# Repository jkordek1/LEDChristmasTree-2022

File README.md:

# LEDChristmasTree-2022

## About
LED Christmas tree powered by 2xAAA batteries. It uses self-flashing LEDs (fast and slow). Device draws ~5 mA of current so the batteries should last through holidays!

There are a lot of LED christmas trees but this one is just a perfect size, uses small amount of power and it gives a really nice effect.

## GIFs and images

## YouTube
https://www.youtube.com/shorts/3aN1jUx8Kqs

## BOM
| #  | QTY | Component | Link
| ------------- | ------------- | ------------- | ------------- |
| 1  | 6 | 0807 RGB LED Fast  | [Aliexpress](https://www.aliexpress.com/item/32816748212.html?spm=a2g0o.order_detail.0.0.6c50f19cJa7Ddi) |
| 2  | 6 | 0807 RGB LED Slow  | [Aliexpress](https://www.aliexpress.com/item/32816748212.html?spm=a2g0o.order_detail.0.0.6c50f19cJa7Ddi) |
| 3  | 1 | 2xAAA Battery holder  | [Aliexpress](https://www.aliexpress.com/item/4001139676299.html?spm=a2g0o.order_list.0.0.21ef18022NrTgV) |
| 4  | 1 |  Slide switch  | [LCSC](https://lcsc.com/product-detail/Slide-Switches_Korean-Hroparts-Elec-K3-1296S-E2_C136659.html) |
| 5  | 12 | 2k 0603 resistor  | - |

## Project folder structure
    .
    ├── ...
    ├── Graphics                # Images and graphics
    ├── KiCadFiles              # Main KiCAD folder
    │   └── jlcpcb              # JLCPCB assembly and gerber folder
    ├── stand 3D model          # .stl file for stand
    └── ...

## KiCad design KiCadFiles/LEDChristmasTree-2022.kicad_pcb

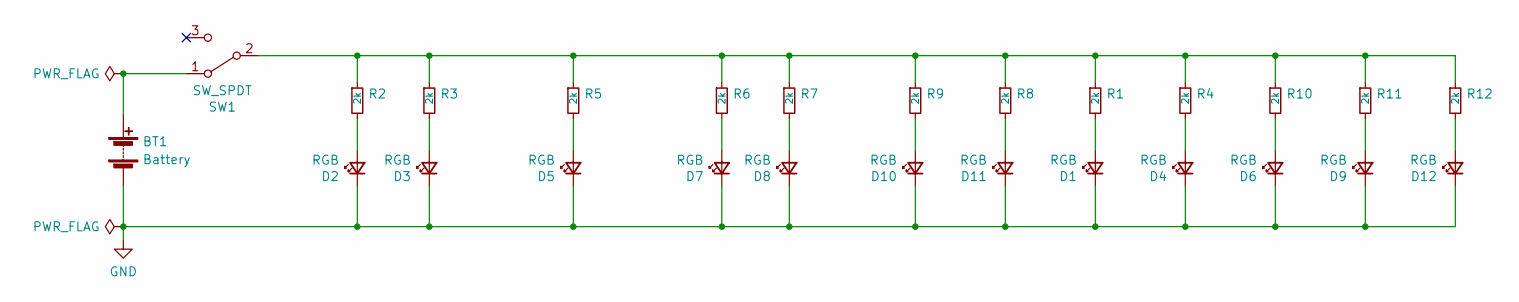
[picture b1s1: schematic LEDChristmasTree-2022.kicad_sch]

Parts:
BT1: Battery; 2xAAA-422-SMT
D1, D2, D3, D4, D5, D6, D7, D8, D9, D10, D11, D12: RGB; LED-0807
R1, R2, R3, R4, R5, R6, R7, R8, R9, R10, R11, R12: 2k; R_0603_1608Metric
SW1: SW_SPDT; SW_SPDT_PCM12

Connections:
GND: BT1.1 (-), D1.1 (K), D2.1 (K), D3.1 (K), D4.1 (K), D5.1 (K), D6.1 (K), D7.1 (K), D8.1 (K), D9.1 (K), D10.1 (K), D11.1 (K), D12.1 (K)
unnamed: BT1.3 (+), SW1.1 (A)
unnamed: D1.2 (A), R1.2
unnamed: D2.2 (A), R2.2
unnamed: D3.2 (A), R3.2
unnamed: D4.2 (A), R4.2
unnamed: D5.2 (A), R5.2
unnamed: D6.2 (A), R10.2
unnamed: D7.2 (A), R6.2
unnamed: D8.2 (A), R7.2
unnamed: D9.2 (A), R11.2
unnamed: D10.2 (A), R9.2
unnamed: D11.2 (A), R8.2
unnamed: D12.2 (A), R12.2
unnamed: R1.1, R2.1, R3.1, R4.1, R5.1, R6.1, R7.1, R8.1, R9.1, R10.1, R11.1, R12.1, SW1.2 (B)

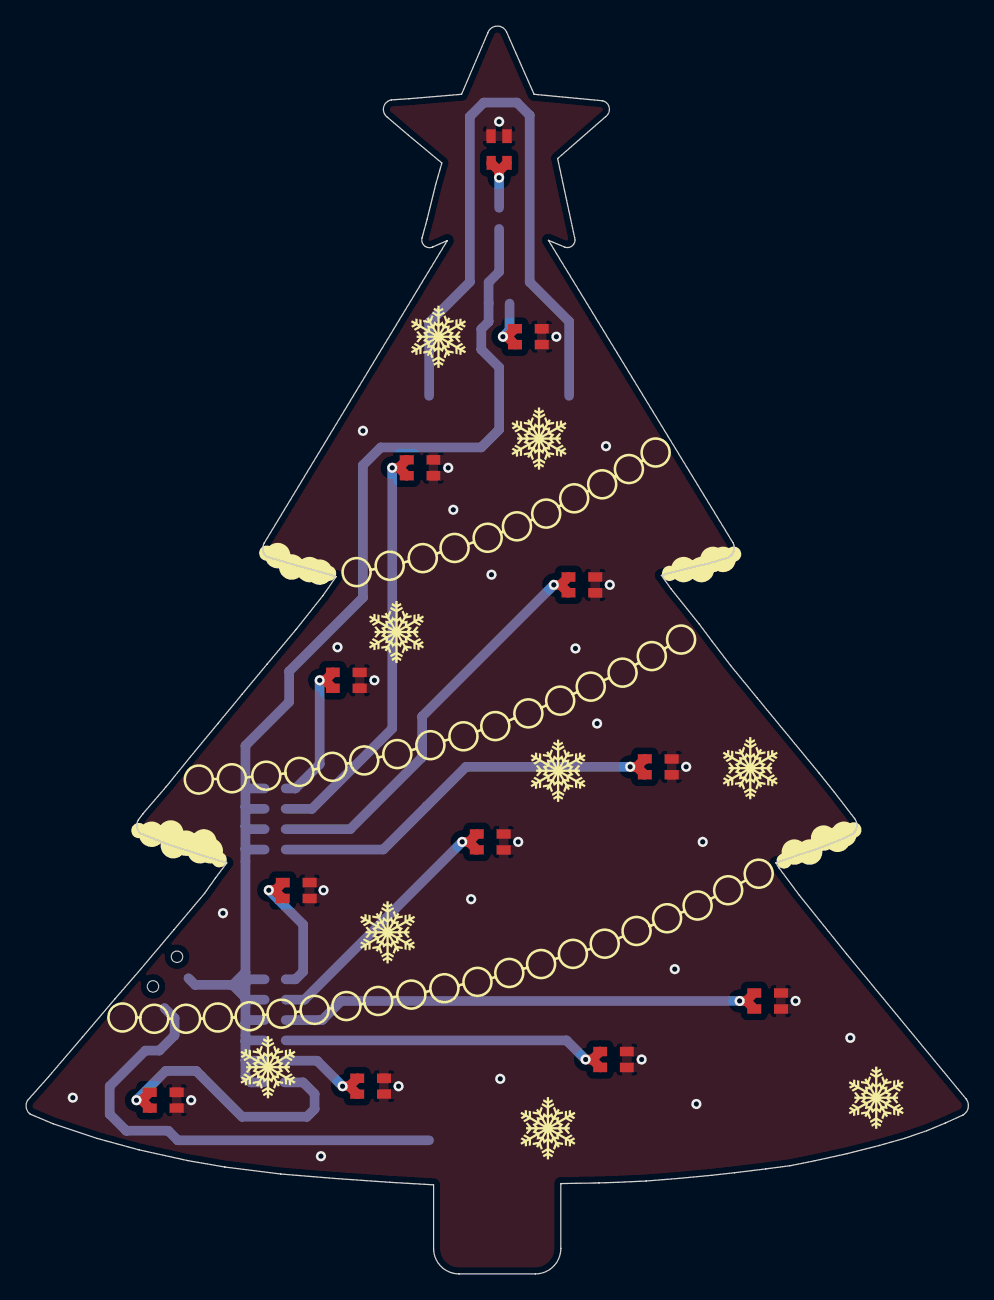
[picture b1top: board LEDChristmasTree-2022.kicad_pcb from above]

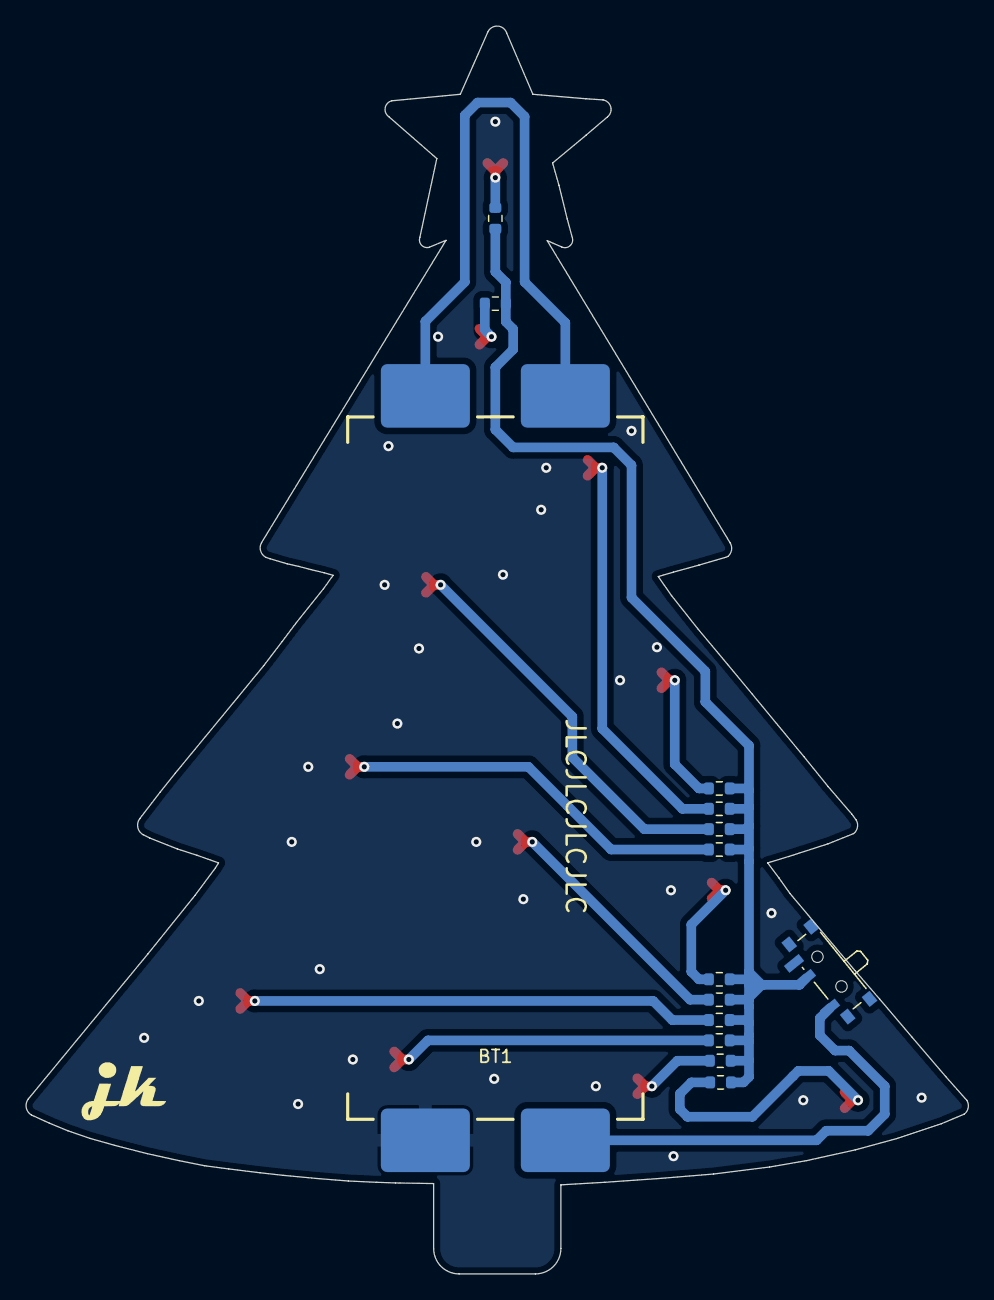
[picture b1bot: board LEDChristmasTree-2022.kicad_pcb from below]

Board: 2 copper layers, 74.0 x 98.1 mm, 26 parts (14 on the bottom side), 15 nets.

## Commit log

2022-02-17 initial
2022-02-23 edge cut
2022-02-28 star
2022-03-01 update1
2022-03-01 layout
2022-03-01 polarity
2022-03-01 gerber
2022-03-02 ukrasi
2022-03-02 backup
2022-03-22 fixed battery polarity
2022-03-28 udate
2022-08-02 jlcpcb
2022-11-27 images
2022-11-27 lightup
2023-04-18 folder structure
